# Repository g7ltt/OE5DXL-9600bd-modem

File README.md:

# OE5DXL-9600bd-modem

This modem has a very comfortable 9600bps operating speed with a suitable radio. 4 separate drivers have been written for the modem, but there is no driver in the Flexnet system .

 L2PCX.EXE Terminal Driver (Single modem) [MS-DOS]

 L2PCX4.EXE Terminal Driver (4 modems) [MS-DOS]

 ax25lib5.tgz JNOS Driver [Linux]

 agwdxl.vxd AGW Driver (Windows 9x, ME, XP)

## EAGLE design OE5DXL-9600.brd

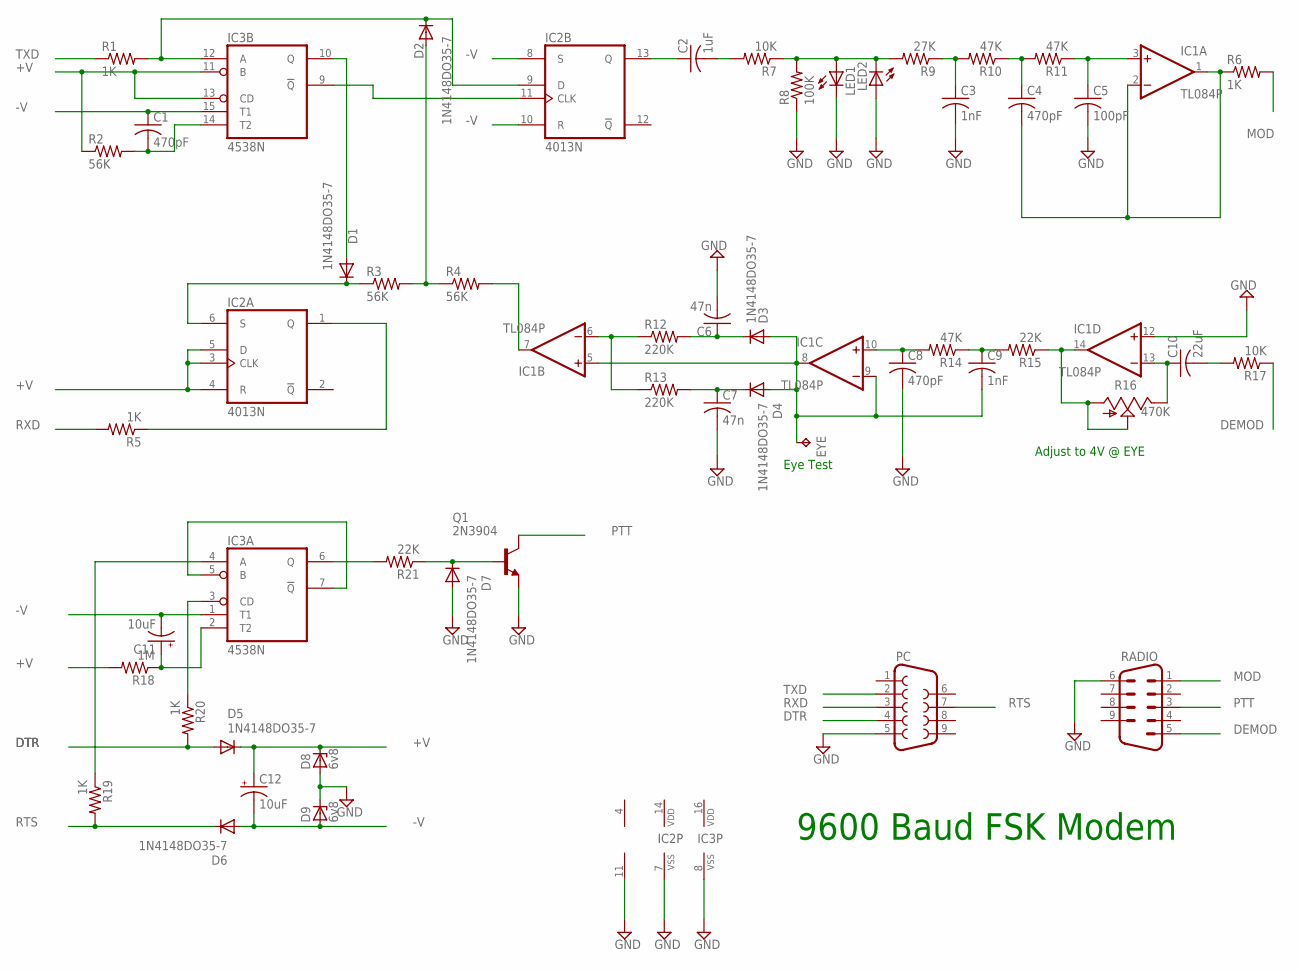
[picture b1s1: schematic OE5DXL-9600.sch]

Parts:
C1, C4, C8: 470pF; C025-025X050
C2: 1uF; C025-025X050
C3, C9: 1nF; C025-025X050
C5: 100pF; C025-025X050
C6, C7: 47n; C025-025X050
C10: 22uF; C025-025X050
C11, C12: 10uF; E2,5-6E
D1, D2, D3, D4, D5, D6, D7: 1N4148DO35-7; DO35-7
D8, D9: 6v8; DO34Z7
EYE: TPPAD1-13; P1-13
IC1: TL084P; DIL14
IC2: 4013N; DIL14
IC3: 4538N; DIL16
LED1, LED2: LED3MM
PC: F09D
Q1: 2N3904; TO92
R1, R5, R6, R19, R20: 1K; 0207/2V
R2, R3, R4: 56K; 0207/2V
R7, R17: 10K; 0207/2V
R8: 100K; 0207/2V
R9: 27K; 0207/2V
R10, R11, R14: 47K; 0207/2V
R12, R13: 220K; 0207/2V
R15, R21: 22K; 0207/2V
R16: 470K; CA6V
R18: 1M; 0207/2V
RADIO: M09D

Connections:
+V: C12.+, D5.C, D8.C, IC2.3 (CLK), IC2.4 (R), IC2.5 (D), IC3.11 (B), IC3.13 (CD), R2.1, R18.2
-V: C1.1, C11.-, C12.-, D6.A, D9.A, IC2.8 (S), IC2.10 (R), IC3.1 (T1), IC3.15 (T1)
DEMOD: R17.1, RADIO.5
DTR: D5.A, PC.4, R20.2
GND: C3.2, C5.2, C6.2, C7.2, C8.2, D7.A, D8.A, D9.C, IC1.11 (V-), IC1.12 (+IN), IC2.7 (VSS), IC3.8 (VSS), LED1.K (C), LED2.A, PC.5, Q1.3 (E), R8.1, RADIO.6
MOD: R6.2, RADIO.1
unnamed: D2.C, IC2.9 (D), IC3.12 (A), R1.2
unnamed: D1.C, IC2.6 (S), R3.1
unnamed: IC2.11 (CLK), IC3.9 (!Q)
unnamed: D1.A, IC3.10 (Q)
unnamed: C1.2, IC3.14 (T2), R2.2
unnamed: D2.A, R3.2, R4.1
unnamed: IC2.1 (Q), R5.1
unnamed: IC1.7 (OUT), R4.2
unnamed: C2.1, IC2.13 (Q)
unnamed: C2.2, R7.2
unnamed: LED1.A, LED2.K (C), R7.1, R8.2, R9.2
unnamed: C3.1, R9.1, R10.2
unnamed: C4.1, R10.1, R11.2
unnamed: C5.1, IC1.3 (+IN), R11.1
unnamed: C4.2, IC1.1 (OUT), IC1.2 (-IN), R6.1
unnamed: IC1.6 (-IN), R12.1, R13.1
unnamed: C6.1, D3.C, R12.2
unnamed: C9.2, D3.A, D4.A, EYE.TP, IC1.5 (+IN), IC1.8 (OUT), IC1.9 (-IN)
unnamed: IC3.5 (B), IC3.7 (!Q)
unnamed: C7.1, D4.C, R13.2
unnamed: C8.1, IC1.10 (+IN), R14.2
unnamed: C9.1, R14.1, R15.2
unnamed: IC1.14 (OUT), R15.1, R16.A, R16.S
unnamed: IC3.4 (A), R19.1
unnamed: C10.1, IC1.13 (-IN), R16.E
unnamed: C11.+, IC3.2 (T2), R18.1
unnamed: C10.2, R17.2
unnamed: IC3.3 (CD), R20.1
unnamed: IC3.6 (Q), R21.2
unnamed: D7.C, Q1.2 (B), R21.1
PTT: Q1.1 (C), RADIO.3
RTS: D6.C, PC.7, R19.2
RXD: PC.3, R5.2
TXD: PC.2, R1.1
V+: IC1.4 (V+)
VDD: IC2.14 (VDD), IC3.16 (VDD)

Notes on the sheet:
9600 Baud FSK Modem
Adjust to 4V @ EYE
Eye Test

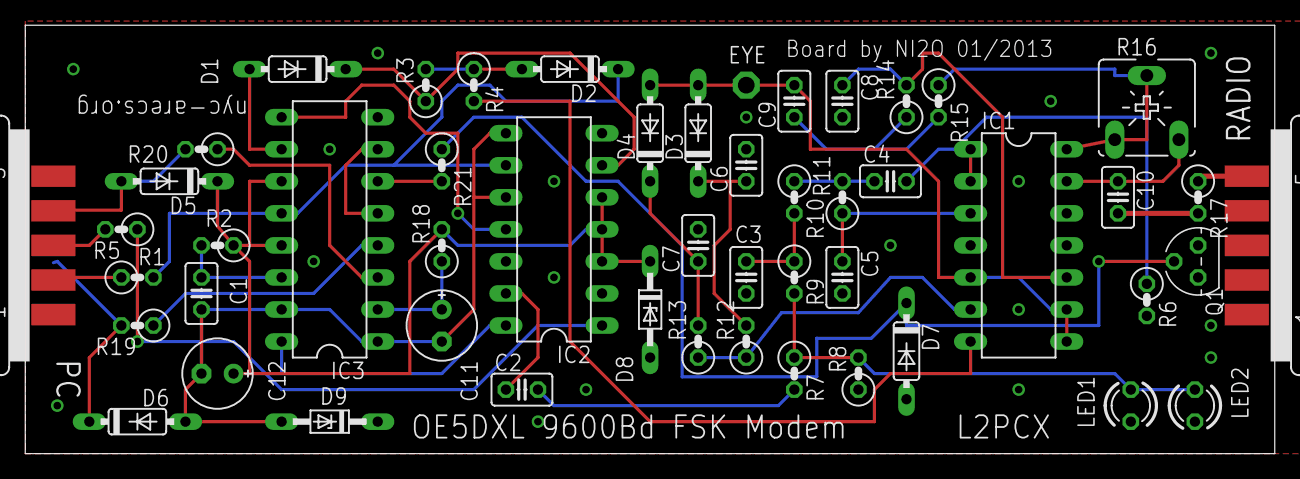
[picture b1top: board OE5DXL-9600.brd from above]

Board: 2 copper layers, 99.0 x 34.0 mm, 51 parts (0 on the bottom side), 41 nets.

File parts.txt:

Exported from OE5DXL-9600.sch at 4/11/14 12:07 PM

Part     Value          Device            Package      Library        Sheet

C1       470pF          C-US025-025X050   C025-025X050 rcl            1
C2       1uF            C-US025-025X050   C025-025X050 rcl            1
C3       1nF            C-US025-025X050   C025-025X050 rcl            1
C4       470pF          C-US025-025X050   C025-025X050 rcl            1
C5       100pF          C-US025-025X050   C025-025X050 rcl            1
C6       47n            C-US025-025X050   C025-025X050 rcl            1
C7       47n            C-US025-025X050   C025-025X050 rcl            1
C8       470pF          C-US025-025X050   C025-025X050 rcl            1
C9       1nF            C-US025-025X050   C025-025X050 rcl            1
C10      22uF           C-US025-025X050   C025-025X050 rcl            1
C11      10uF           CPOL-USE2,5-6E    E2,5-6E      rcl            1
C12      10uF           CPOL-USE2,5-6E    E2,5-6E      rcl            1
D1       1N4148DO35-7   1N4148DO35-7      DO35-7       diode          1
D2       1N4148DO35-7   1N4148DO35-7      DO35-7       diode          1
D3       1N4148DO35-7   1N4148DO35-7      DO35-7       diode          1
D4       1N4148DO35-7   1N4148DO35-7      DO35-7       diode          1
D5       1N4148DO35-7   1N4148DO35-7      DO35-7       diode          1
D6       1N4148DO35-7   1N4148DO35-7      DO35-7       diode          1
D7       1N4148DO35-7   1N4148DO35-7      DO35-7       diode          1
D8       6v8            ZENER-DIODEDO34-7 DO34Z7       diode          1
D9       6v8            ZENER-DIODEDO34-7 DO34Z7       diode          1
EYE      TPPAD1-13      TPPAD1-13         P1-13        testpad        1
IC1      TL084P         TL084P            DIL14        linear         1
IC2      4013N          4013N             DIL14        40xx           1
IC3      4538N          4538N             DIL16        45xx           1
LED1                    LED3MM            LED3MM       led            1
LED2                    LED3MM            LED3MM       led            1
PC                      F09D              F09D         con-subd       1
Q1       2N3904         2N3904            TO92         transistor-npn 1
R1       1K             R-US_0207/2V      0207/2V      rcl            1
R2       56K            R-US_0207/2V      0207/2V      rcl            1
R3       56K            R-US_0207/2V      0207/2V      rcl            1
R4       56K            R-US_0207/2V      0207/2V      rcl            1
R5       1K             R-US_0207/2V      0207/2V      rcl            1
R6       1K             R-US_0207/2V      0207/2V      rcl            1
R7       10K            R-US_0207/2V      0207/2V      rcl            1
R8       100K           R-US_0207/2V      0207/2V      rcl            1
R9       27K            R-US_0207/2V      0207/2V      rcl            1
R10      47K            R-US_0207/2V      0207/2V      rcl            1
R11      47K            R-US_0207/2V      0207/2V      rcl            1
R12      220K           R-US_0207/2V      0207/2V      rcl            1
R13      220K           R-US_0207/2V      0207/2V      rcl            1
R14      47K            R-US_0207/2V      0207/2V      rcl            1
R15      22K            R-US_0207/2V      0207/2V      rcl            1
R16      470K           TRIM_US-CA6V      CA6V         pot            1
R17      10K            R-US_0207/2V      0207/2V      rcl            1
R18      1M             R-US_0207/2V      0207/2V      rcl            1
R19      1K             R-US_0207/2V      0207/2V      rcl            1
R20      1K             R-US_0207/2V      0207/2V      rcl            1
R21      22K            R-US_0207/2V      0207/2V      rcl            1
RADIO                   M09D              M09D         con-subd       1
